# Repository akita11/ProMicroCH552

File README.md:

# ProMicroCH552

[WCH(南京沁恒微电子股份有限公司)](http://wch-ic.com/)の8ビットマイコン[CH552](http://wch-ic.com/products/CH552.html)を使った、ProMicro型のマイコンボードです。
主な特徴は以下のとおりです。

- ProMicro型
- [ArduinoIDEなどでプログラム開発が可能](https://qiita.com/akita11/items/d7baed4ca3c06e292637)
- USBペリフェラル（キーボードやUSBメモリなど）として動作可能
- USB Type-Cコネクタ

またProMicroとは、以下のような違いがあります。
- 一部ピンの機能が異なる
- 一部未接続の端子がある
- +3.3V出力の電流供給能力は100mA程度（CH552内蔵レギュレータの性能）
- リセット(RST)は正論理で、"1"でリセット
- +5V端子に、外部電源から+5Vを供給可能（内部にレギュレータはないので、+5Vを超える電圧は不可）

## ピン配置

基板上の"LED"（オレンジ）はP1.7で駆動できます。

# 訂正

基板上の2個のシルク表示が逆になっているロットがあります。正しくは、R4側が"LED"（オレンジ）、反対側が"POW"（緑、電源インジケータ）です。

## Author

Junichi Akita (@akita11) / akita@ifdl.jp

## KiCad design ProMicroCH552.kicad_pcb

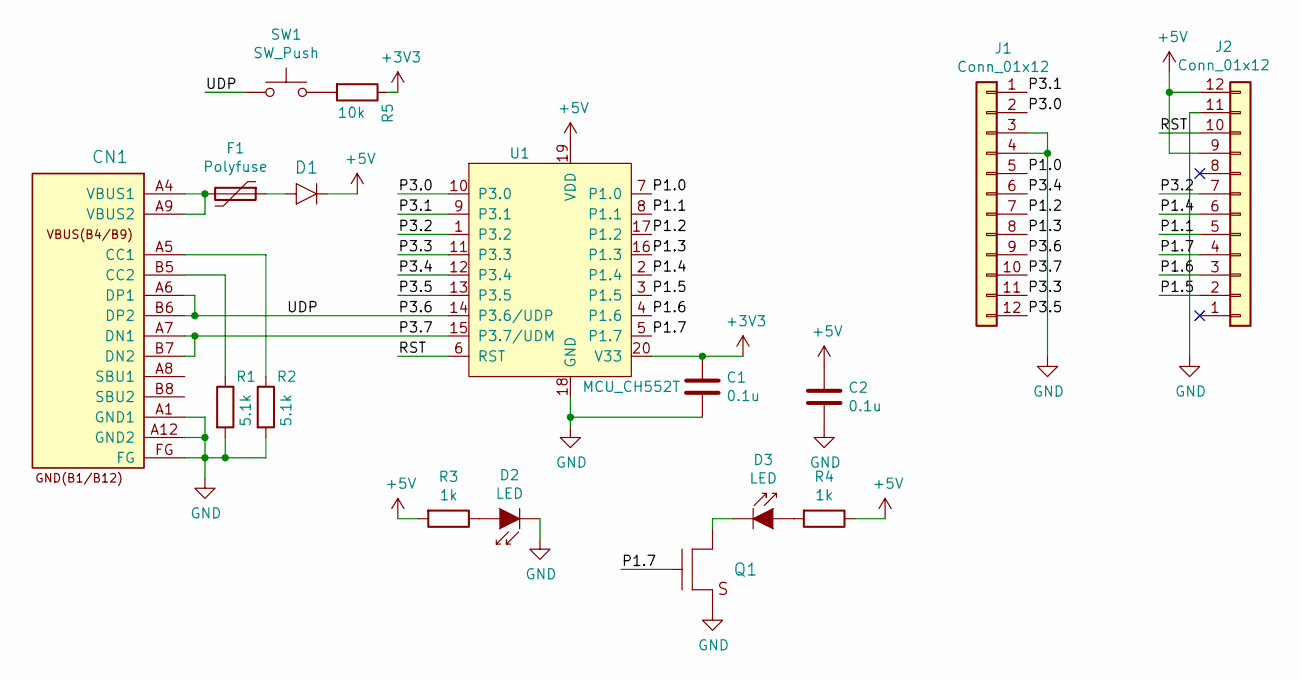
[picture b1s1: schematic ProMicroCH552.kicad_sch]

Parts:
C1, C2: 0.1u; C_0603_1608Metric
CN1: CON_USB-C-16; USB-C_16P_TH
D1: DIODE; D_SOD123FL
D2, D3: LED; LED_0603_1608Metric
F1: Polyfuse; R_1210_3225Metric
J1, J2: Conn_01x12; PinSocket_1x12_P2.54mm_Vertical
Q1: TR_NMOS_IRLML6344; SOT-23
R1, R2: 5.1k; R_0603_1608Metric
R3, R4: 1k; R_0603_1608Metric
R5: 10k; R_0603_1608Metric
SW1: SW_Push; SW_Push_SPST_NO_Alps_SKRK
U1: MCU_CH552T; TSSOP-20_4.4x6.5mm_P0.65mm

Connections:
+3V3: C1.1, R5.1, U1.20 (V33)
+5V: C2.1, D1.K, J2.9, J2.12, R3.2, R4.1, U1.19 (VDD)
/P1.0: J1.5, U1.7 (P1.0)
/P1.1: J2.5, U1.8 (P1.1)
/P1.2: J1.7, U1.17 (P1.2)
/P1.3: J1.8, U1.16 (P1.3)
/P1.4: J2.6, U1.2 (P1.4)
/P1.5: J2.2, U1.3 (P1.5)
/P1.6: J2.3, U1.4 (P1.6)
/P1.7: J2.4, Q1.1 (G), U1.5 (P1.7)
/P3.0: J1.2, U1.10 (P3.0)
/P3.1: J1.1, U1.9 (P3.1)
/P3.2: J2.7, U1.1 (P3.2)
/P3.3: J1.11, U1.11 (P3.3)
/P3.4: J1.6, U1.12 (P3.4)
/P3.5: J1.12, U1.13 (P3.5)
/P3.6: CN1.A6 (DP1), CN1.B6 (DP2), J1.9, SW1.1, U1.14 (P3.6/UDP)
/P3.7: CN1.A7 (DN1), CN1.B7 (DN2), J1.10, U1.15 (P3.7/UDM)
/RST: J2.10, U1.6 (RST)
GND: C1.2, C2.2, CN1.A1 (GND1), CN1.A12 (GND2), CN1.FG, D2.1 (K), J1.3, J1.4, J2.11, Q1.2 (S), R1.2, R2.2, U1.18 (GND)
unnamed: CN1.A4 (VBUS1), CN1.A9 (VBUS2), F1.2
unnamed: CN1.A5 (CC1), R2.1
unnamed: CN1.B5 (CC2), R1.1
unnamed: D1.A, F1.1
unnamed: D2.2 (A), R3.1
unnamed: D3.1 (K), Q1.3 (D)
unnamed: D3.2 (A), R4.2
unnamed: R5.2, SW1.2

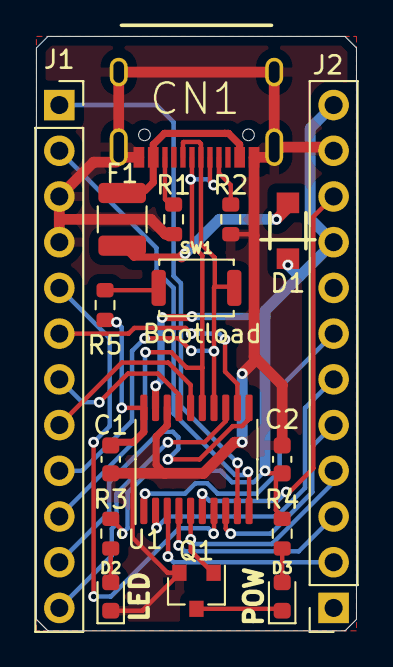
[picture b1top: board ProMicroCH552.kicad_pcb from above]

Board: 2 copper layers, 17.8 x 33.0 mm, 17 parts (0 on the bottom side), 28 nets.

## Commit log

2022-01-19 シルク修正、KiCAD6
2022-01-19 pin map
2022-01-20 resize pin map image
2022-01-20 外部電源について追記
2022-01-26 add image
2022-01-28 +3.3V出力電流について追記
2022-01-28 add schematic
